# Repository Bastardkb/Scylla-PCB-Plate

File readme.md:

# Scylla PCB - plate

Flexible PCB made for the Scylla.

With per-key RGB.

This repository contains all files necessary to order a PCB.

If you want to modify the design files, the Kicad sources are included.
<!-- If you just want to order the PCBs, check out the Release section which contain the gerber files. -->

## How to order

Order with a 0.6mm or 0.8mm PCB thickness

## License

Licensed under CC BY-NC-SA 4.0
Copyright Quentin Lebastard 2021

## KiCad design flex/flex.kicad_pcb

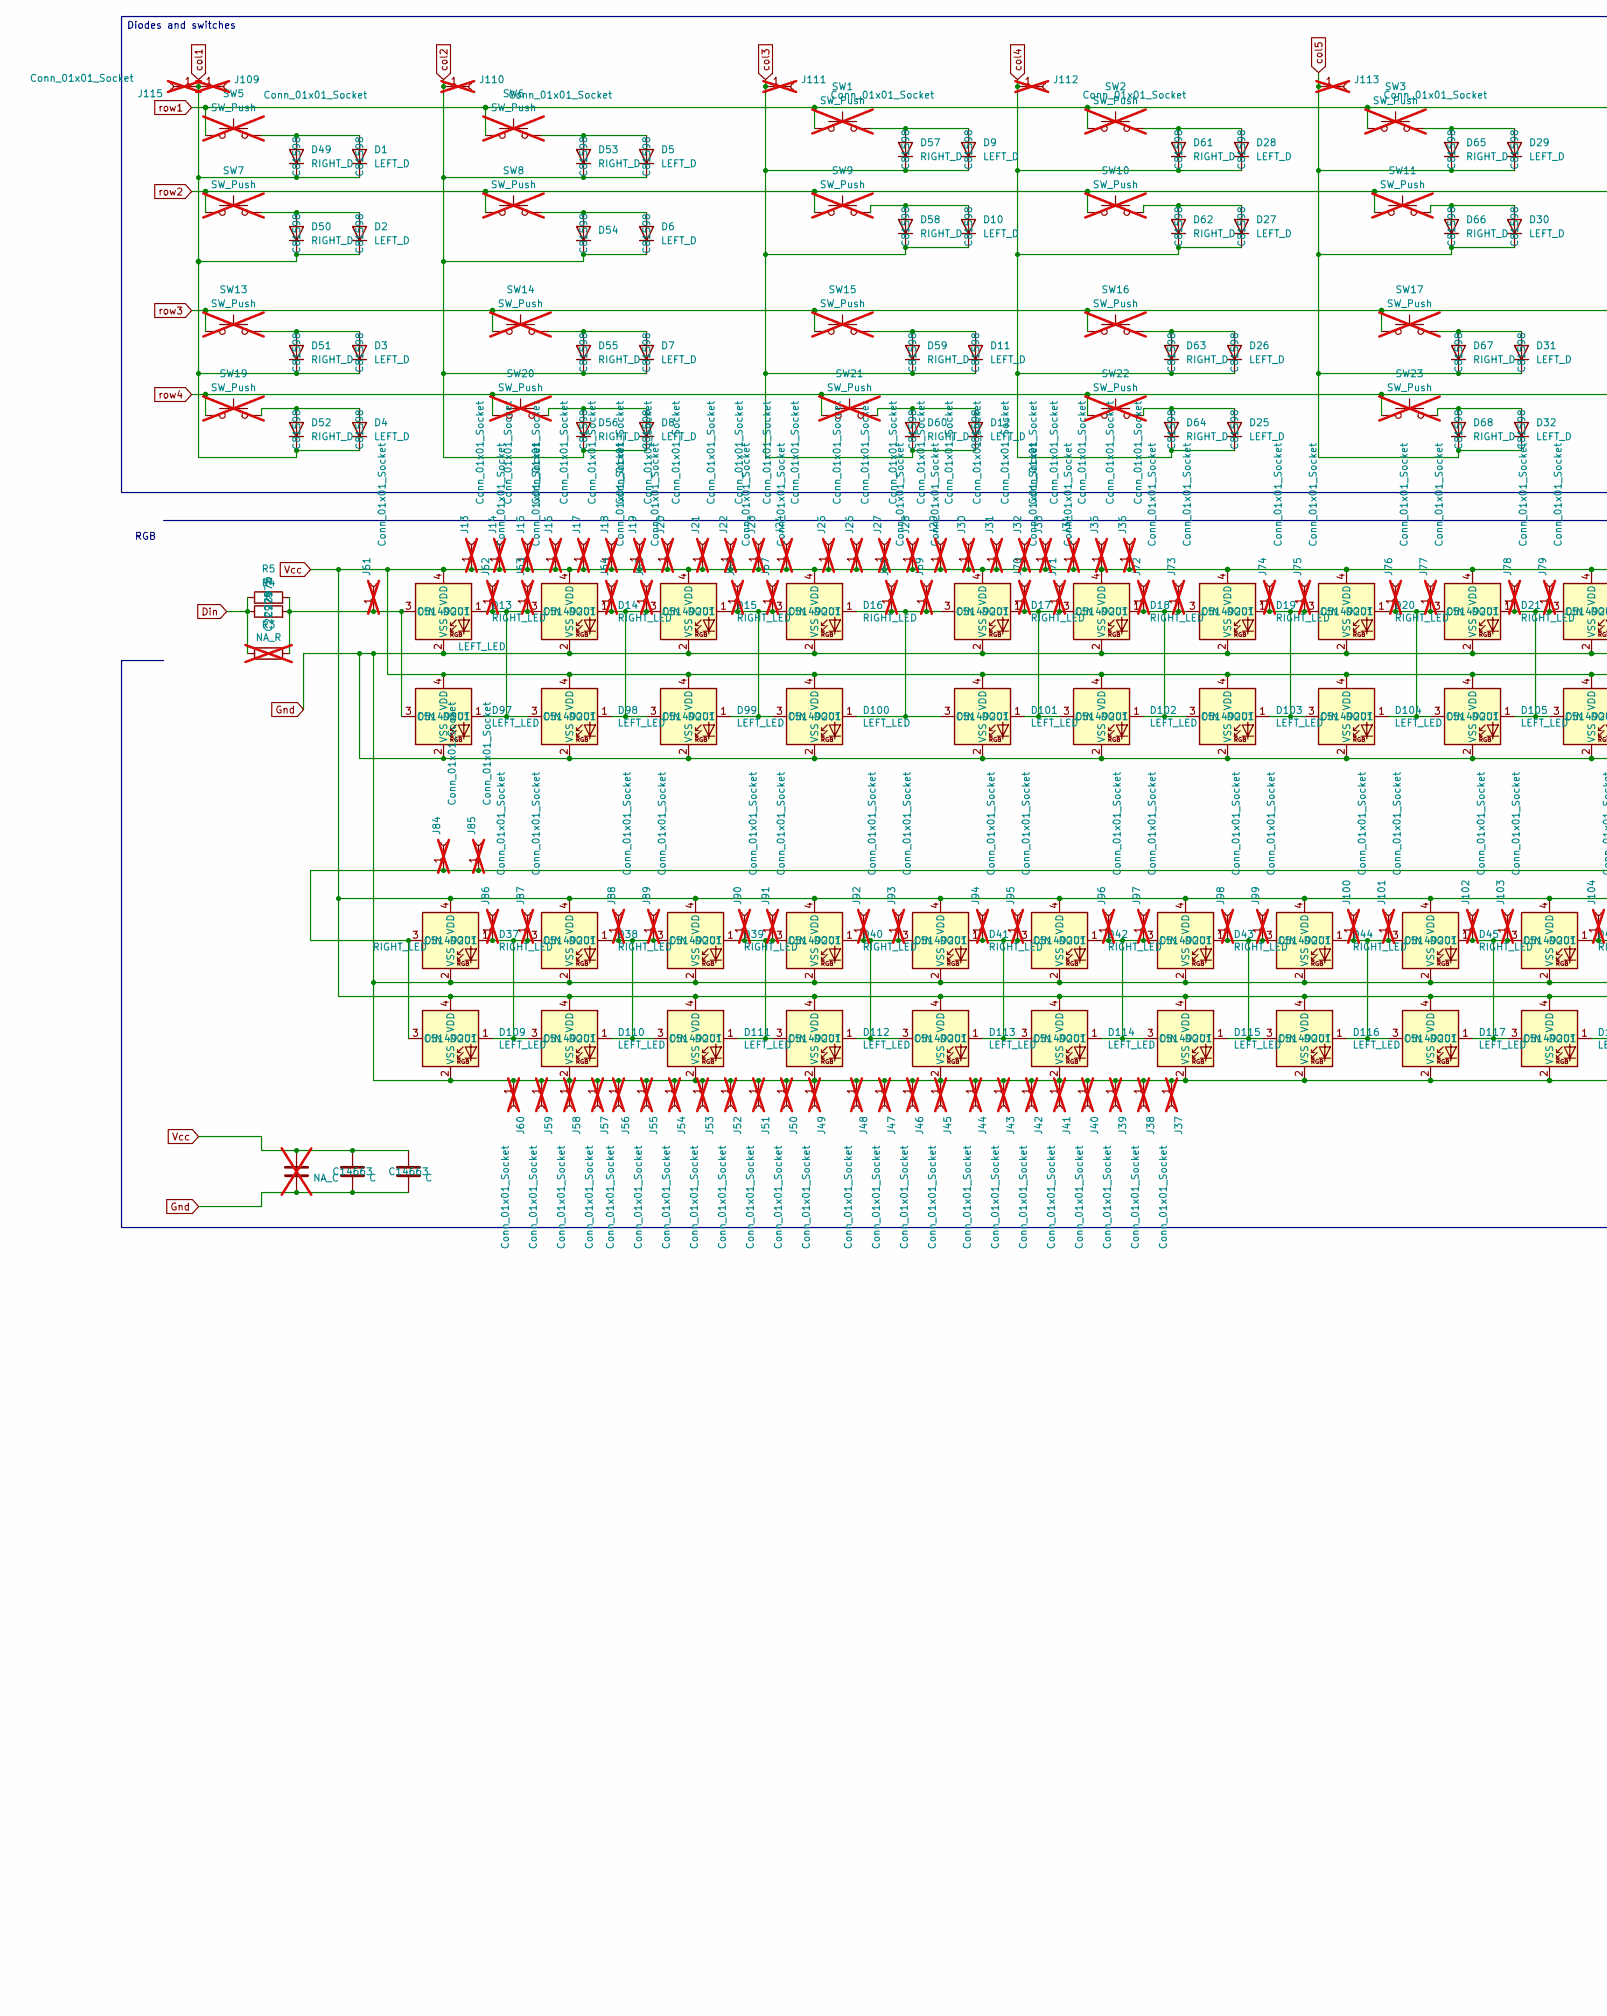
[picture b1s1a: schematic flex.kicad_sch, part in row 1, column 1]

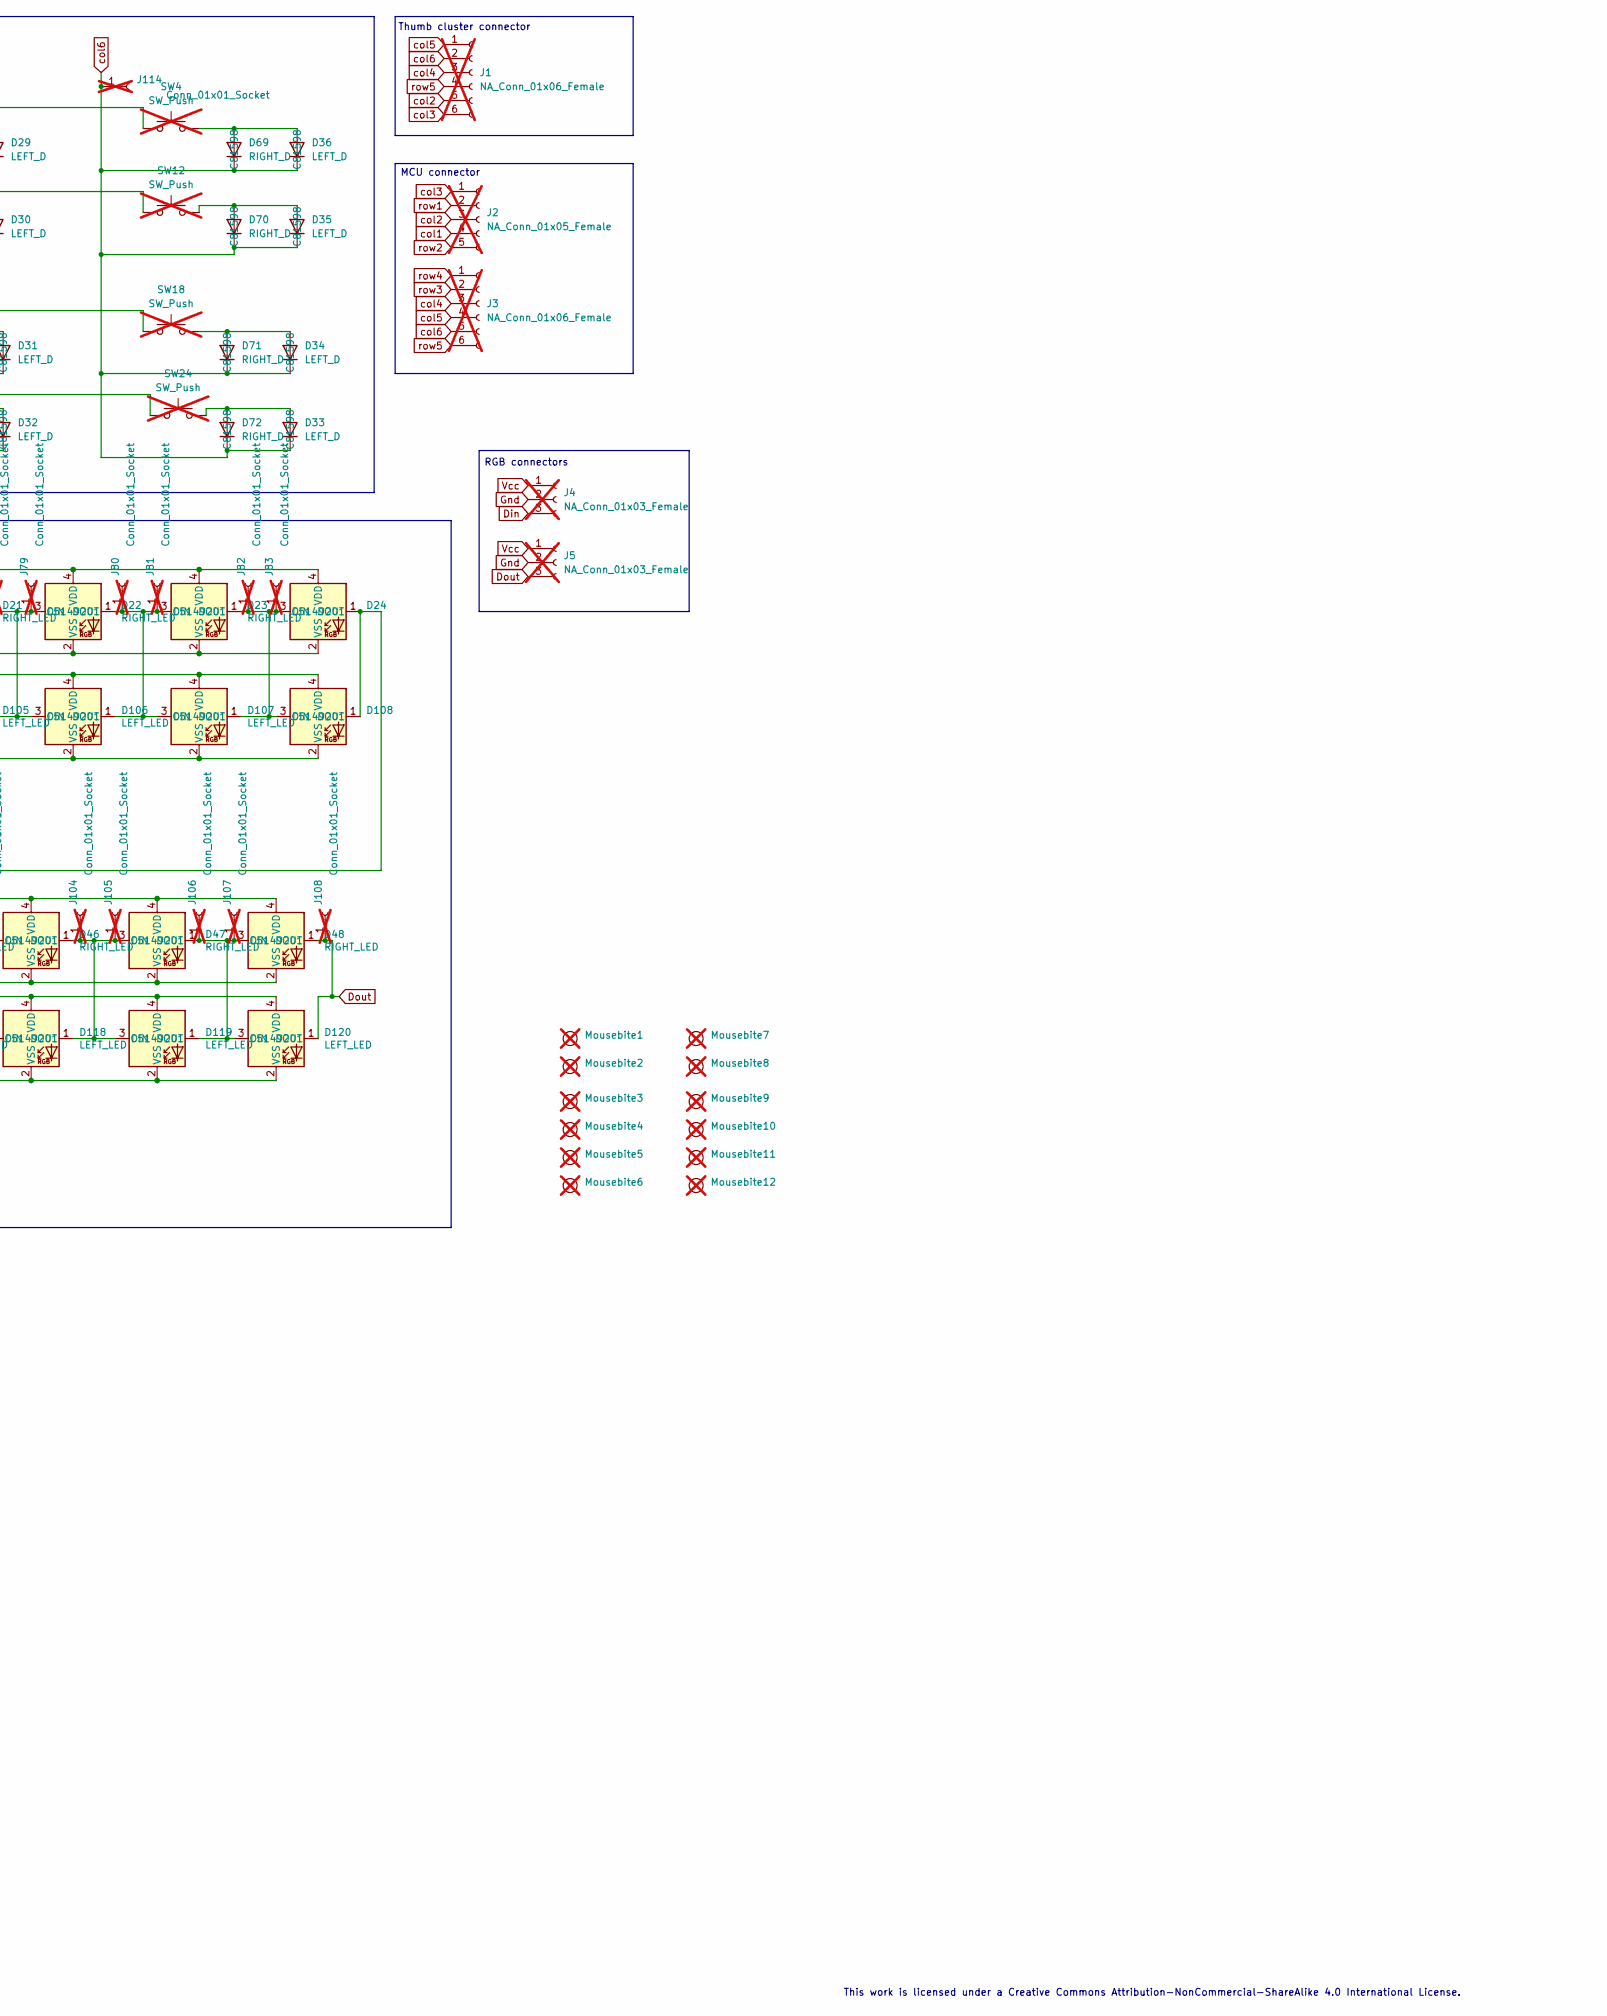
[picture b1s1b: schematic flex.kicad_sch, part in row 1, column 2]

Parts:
C3: NA_C; C_SOD123; not fitted
C4, C5: C; C_0603_1608Metric; LCSC C14663
D1, D2, D3, D4, D5, D6, D7, D8, D9, D10, D11, D12, D25, D26, D27, D28, D29, D30, D31, D32, D33, D34, D35, D36: LEFT_D; SOD123_assembly; LCSC C81598
D13, D14, D15, D16, D17, D18, D19, D20, D21, D22, D23, D24, D37, D38, D39, D40, D41, D42, D43, D44, D45, D46, D47, D48: RIGHT_LED; SK6812_mini_e_corners; LCSC C5149201
D49, D50, D51, D52, D53, D54, D55, D56, D57, D58, D59, D60, D61, D62, D63, D64, D65, D66, D67, D68, D69, D70, D71, D72: RIGHT_D; SOD123_assembly; LCSC C81598
D97, D98, D99, D100, D101, D102, D103, D104, D105, D106, D107, D108, D109, D110, D111, D112, D113, D114, D115, D116, D117, D118, D119, D120: LEFT_LED; SK6812_mini_e_corners_noedgecuts; LCSC C5149201
J1, J3: NA_Conn_01x06_Female; PinHeader_1x06_P2.54mm_Vertical; not fitted
J2: NA_Conn_01x05_Female; PinHeader_1x05_P2.54mm_Vertical; not fitted
J4, J5: NA_Conn_01x03_Female; PinHeader_1x03_P2.54mm_Vertical; not fitted
J13, J14, J15, J16, J17, J18, J19, J20, J21, J22, J23, J24, J25, J26, J27, J28, J29, J30, J31, J32, J33, J34, J35, J36: Conn_01x01_Socket; PinHeader_1x01_P1.27mm_Vertical_VCC; not fitted
J37, J38, J39, J40, J41, J42, J43, J44, J45, J46, J47, J48, J49, J50, J51, J52, J53, J54, J55, J56, J57, J58, J59, J60: Conn_01x01_Socket; PinHeader_1x01_P1.27mm_Vertical_GND; not fitted
J61, J63, J65, J67, J69, J71, J73, J75, J77, J79, J81, J83, J84, J87, J89, J91, J93, J95, J97, J99, J101, J103, J105, J107: Conn_01x01_Socket; PinHeader_1x01_P1.27mm_Vertical_IN; not fitted
J62, J64, J66, J68, J70, J72, J74, J76, J78, J80, J82, J85, J86, J88, J90, J92, J94, J96, J98, J100, J102, J104, J106, J108: Conn_01x01_Socket; PinHeader_1x01_P1.27mm_Vertical_OUT; not fitted
J109, J110, J111, J112, J113, J114, J115: Conn_01x01_Socket; PinHeader_1x01_P1.27mm_Vertical; not fitted
Mousebite1, Mousebite2, Mousebite3, Mousebite4, Mousebite5, Mousebite6, Mousebite7, Mousebite8, Mousebite9, Mousebite10, Mousebite11, Mousebite12: mousebite; not fitted
R3: NA_R; R_SOD123; not fitted
R4, R5: R; R_0603_1608Metric; LCSC C22975
SW1, SW2, SW3, SW4, SW5, SW6, SW7, SW8, SW9, SW10, SW11, SW12, SW13, SW14, SW15, SW16, SW17, SW18, SW19, SW20, SW21, SW22, SW23, SW24: SW_Push; SW_MX_reversible; not fitted

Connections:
Din: J4.3, R3.1, R4.1, R5.1
Dout: D48.1 (DOUT), D120.1 (DOUT), J5.3, J108.1
Gnd: C3.2, C4.2, C5.2, D13.2 (VSS), D14.2 (VSS), D15.2 (VSS), D16.2 (VSS), D17.2 (VSS), D18.2 (VSS), D19.2 (VSS), D20.2 (VSS), D21.2 (VSS), D22.2 (VSS), D23.2 (VSS), D24.2 (VSS), D37.2 (VSS), D38.2 (VSS), D39.2 (VSS), D40.2 (VSS), D41.2 (VSS), D42.2 (VSS), D43.2 (VSS), D44.2 (VSS), D45.2 (VSS), D46.2 (VSS), D47.2 (VSS), D48.2 (VSS), D97.2 (VSS), D98.2 (VSS), D99.2 (VSS), D100.2 (VSS), D101.2 (VSS), D102.2 (VSS), D103.2 (VSS), D104.2 (VSS), D105.2 (VSS), D106.2 (VSS), D107.2 (VSS), D108.2 (VSS), D109.2 (VSS), D110.2 (VSS), D111.2 (VSS), D112.2 (VSS), D113.2 (VSS), D114.2 (VSS), D115.2 (VSS), D116.2 (VSS), D117.2 (VSS), D118.2 (VSS), D119.2 (VSS), D120.2 (VSS), J4.2, J5.2, J37.1, J38.1, J39.1, J40.1, J41.1, J42.1, J43.1, J44.1, J45.1, J46.1, J47.1, J48.1, J49.1, J50.1, J51.1, J52.1, J53.1, J54.1, J55.1, J56.1, J57.1, J58.1, J59.1, J60.1
unnamed: D1.2 (A), D49.2 (A), SW5.2
unnamed: D2.2 (A), D50.2 (A), SW7.2
unnamed: D3.2 (A), D51.2 (A), SW13.2
unnamed: D4.2 (A), D52.2 (A), SW19.2
unnamed: D5.2 (A), D53.2 (A), SW6.2
unnamed: D10.2 (A), D58.2 (A), SW9.2
unnamed: D11.2 (A), D59.2 (A), SW15.2
unnamed: D12.2 (A), D60.2 (A), SW21.2
unnamed: D13.3 (DIN), D97.3 (DIN), J61.1, R3.2, R4.2, R5.2
unnamed: D13.1 (DOUT), D14.3 (DIN), D97.1 (DOUT), D98.3 (DIN), J62.1, J63.1
unnamed: D14.1 (DOUT), D15.3 (DIN), D98.1 (DOUT), D99.3 (DIN), J64.1, J65.1
unnamed: D25.2 (A), D64.2 (A), SW22.2
unnamed: D26.2 (A), D63.2 (A), SW16.2
unnamed: D27.2 (A), D62.2 (A), SW10.2
unnamed: D28.2 (A), D61.2 (A), SW2.2
unnamed: D29.2 (A), D65.2 (A), SW3.2
unnamed: D30.2 (A), D66.2 (A), SW11.2
unnamed: D31.2 (A), D67.2 (A), SW17.2
unnamed: D32.2 (A), D68.2 (A), SW23.2
unnamed: D33.2 (A), D72.2 (A), SW24.2
unnamed: D34.2 (A), D71.2 (A), SW18.2
unnamed: D35.2 (A), D70.2 (A), SW12.2
unnamed: D36.2 (A), D69.2 (A), SW4.2
unnamed: D6.2 (A), D54.2 (A), SW8.2
unnamed: D7.2 (A), D55.2 (A), SW14.2
unnamed: D8.2 (A), D56.2 (A), SW20.2
unnamed: D9.2 (A), D57.2 (A), SW1.2
unnamed: D15.1 (DOUT), D16.3 (DIN), D99.1 (DOUT), D100.3 (DIN), J66.1, J67.1
unnamed: D16.1 (DOUT), D17.3 (DIN), D100.1 (DOUT), D101.3 (DIN), J68.1, J69.1
unnamed: D17.1 (DOUT), D18.3 (DIN), D101.1 (DOUT), D102.3 (DIN), J70.1, J71.1
unnamed: D18.1 (DOUT), D19.3 (DIN), D102.1 (DOUT), D103.3 (DIN), J72.1, J73.1
unnamed: D19.1 (DOUT), D20.3 (DIN), D103.1 (DOUT), D104.3 (DIN), J74.1, J75.1
unnamed: D20.1 (DOUT), D21.3 (DIN), D104.1 (DOUT), D105.3 (DIN), J76.1, J77.1
unnamed: D21.1 (DOUT), D22.3 (DIN), D105.1 (DOUT), D106.3 (DIN), J78.1, J79.1
unnamed: D22.1 (DOUT), D23.3 (DIN), D106.1 (DOUT), D107.3 (DIN), J80.1, J81.1
unnamed: D23.1 (DOUT), D24.3 (DIN), D107.1 (DOUT), D108.3 (DIN), J82.1, J83.1
unnamed: D24.1 (DOUT), D37.3 (DIN), D108.1 (DOUT), D109.3 (DIN), J84.1, J85.1
unnamed: D37.1 (DOUT), D38.3 (DIN), D109.1 (DOUT), D110.3 (DIN), J86.1, J87.1
unnamed: D38.1 (DOUT), D39.3 (DIN), D110.1 (DOUT), D111.3 (DIN), J88.1, J89.1
unnamed: D39.1 (DOUT), D40.3 (DIN), D111.1 (DOUT), D112.3 (DIN), J90.1, J91.1
unnamed: D40.1 (DOUT), D41.3 (DIN), D112.1 (DOUT), D113.3 (DIN), J92.1, J93.1
unnamed: D41.1 (DOUT), D42.3 (DIN), D113.1 (DOUT), D114.3 (DIN), J94.1, J95.1
unnamed: D42.1 (DOUT), D43.3 (DIN), D114.1 (DOUT), D115.3 (DIN), J96.1, J97.1
unnamed: D43.1 (DOUT), D44.3 (DIN), D115.1 (DOUT), D116.3 (DIN), J98.1, J99.1
unnamed: D44.1 (DOUT), D45.3 (DIN), D116.1 (DOUT), D117.3 (DIN), J100.1, J101.1
unnamed: D45.1 (DOUT), D46.3 (DIN), D117.1 (DOUT), D118.3 (DIN), J102.1, J103.1
unnamed: D46.1 (DOUT), D47.3 (DIN), D118.1 (DOUT), D119.3 (DIN), J104.1, J105.1
unnamed: D47.1 (DOUT), D48.3 (DIN), D119.1 (DOUT), D120.3 (DIN), J106.1, J107.1
Vcc: C3.1, C4.1, C5.1, D13.4 (VDD), D14.4 (VDD), D15.4 (VDD), D16.4 (VDD), D17.4 (VDD), D18.4 (VDD), D19.4 (VDD), D20.4 (VDD), D21.4 (VDD), D22.4 (VDD), D23.4 (VDD), D24.4 (VDD), D37.4 (VDD), D38.4 (VDD), D39.4 (VDD), D40.4 (VDD), D41.4 (VDD), D42.4 (VDD), D43.4 (VDD), D44.4 (VDD), D45.4 (VDD), D46.4 (VDD), D47.4 (VDD), D48.4 (VDD), D97.4 (VDD), D98.4 (VDD), D99.4 (VDD), D100.4 (VDD), D101.4 (VDD), D102.4 (VDD), D103.4 (VDD), D104.4 (VDD), D105.4 (VDD), D106.4 (VDD), D107.4 (VDD), D108.4 (VDD), D109.4 (VDD), D110.4 (VDD), D111.4 (VDD), D112.4 (VDD), D113.4 (VDD), D114.4 (VDD), D115.4 (VDD), D116.4 (VDD), D117.4 (VDD), D118.4 (VDD), D119.4 (VDD), D120.4 (VDD), J4.1, J5.1, J13.1, J14.1, J15.1, J16.1, J17.1, J18.1, J19.1, J20.1, J21.1, J22.1, J23.1, J24.1, J25.1, J26.1, J27.1, J28.1, J29.1, J30.1, J31.1, J32.1, J33.1, J34.1, J35.1, J36.1
col1: D1.1 (K), D2.1 (K), D3.1 (K), D4.1 (K), D49.1 (K), D50.1 (K), D51.1 (K), D52.1 (K), J2.4, J109.1, J115.1
col2: D5.1 (K), D6.1 (K), D7.1 (K), D8.1 (K), D53.1 (K), D54.1 (K), D55.1 (K), D56.1 (K), J1.5, J2.3, J110.1
col3: D9.1 (K), D10.1 (K), D11.1 (K), D12.1 (K), D57.1 (K), D58.1 (K), D59.1 (K), D60.1 (K), J1.6, J2.1, J111.1
col4: D25.1 (K), D26.1 (K), D27.1 (K), D28.1 (K), D61.1 (K), D62.1 (K), D63.1 (K), D64.1 (K), J1.3, J3.3, J112.1
col5: D29.1 (K), D30.1 (K), D31.1 (K), D32.1 (K), D65.1 (K), D66.1 (K), D67.1 (K), D68.1 (K), J1.1, J3.4, J113.1
col6: D33.1 (K), D34.1 (K), D35.1 (K), D36.1 (K), D69.1 (K), D70.1 (K), D71.1 (K), D72.1 (K), J1.2, J3.5, J114.1
row1: J2.2, SW1.1, SW2.1, SW3.1, SW4.1, SW5.1, SW6.1
row2: J2.5, SW7.1, SW8.1, SW9.1, SW10.1, SW11.1, SW12.1
row3: J3.2, SW13.1, SW14.1, SW15.1, SW16.1, SW17.1, SW18.1
row4: J3.1, SW19.1, SW20.1, SW21.1, SW22.1, SW23.1, SW24.1
row5: J1.4, J3.6

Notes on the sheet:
Diodes and switches
RGB
MCU connector
Thumb cluster connector
This work is licensed under a Creative Commons Attribution-NonCommercial-ShareAlike 4.0 International License.
RGB connectors

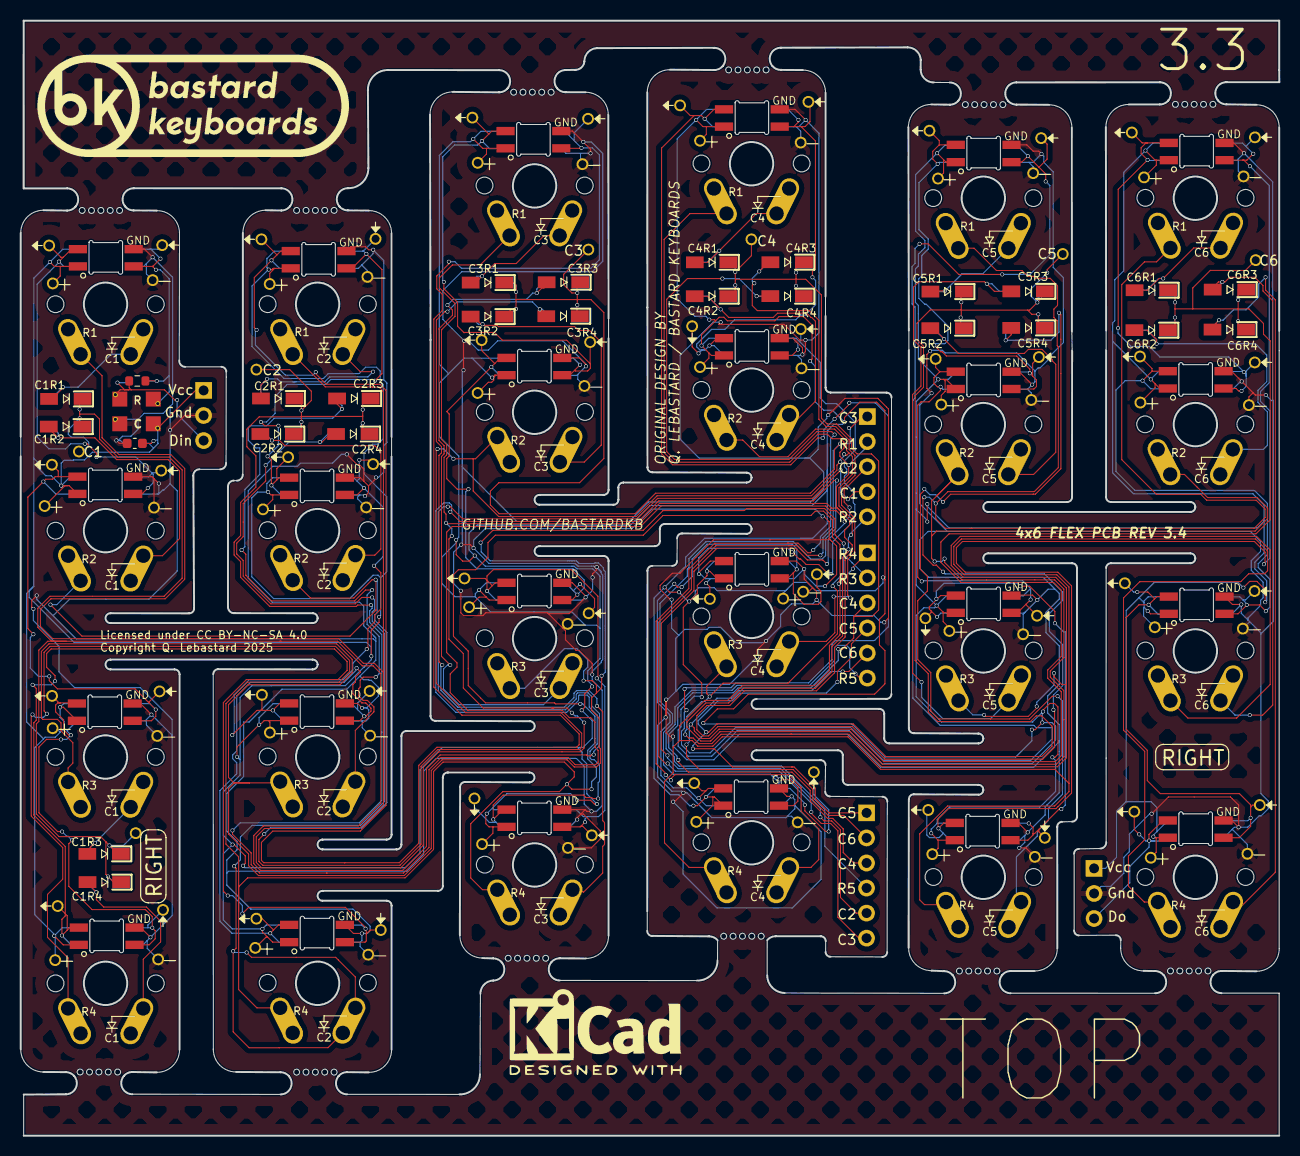
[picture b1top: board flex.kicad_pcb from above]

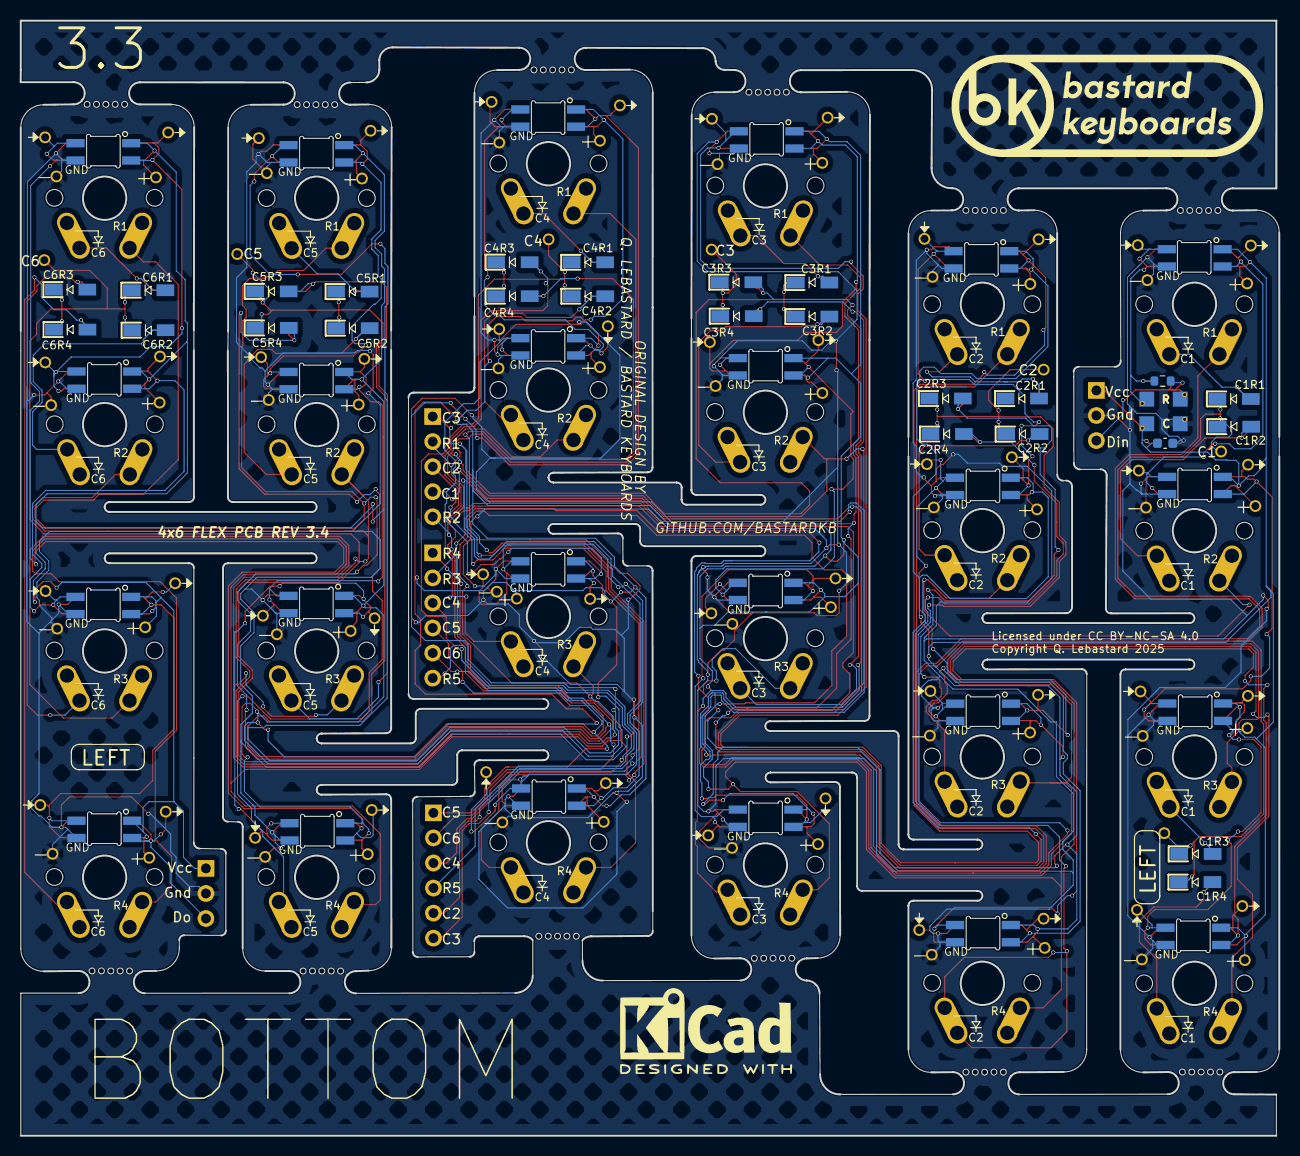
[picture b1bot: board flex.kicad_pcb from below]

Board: 2 copper layers, 127.6 x 113.0 mm, 246 parts (75 on the bottom side), 63 nets.

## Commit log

2022-02-20 add stuff
2022-02-20 edge cuts, via size
2022-02-20 cleanup
2022-02-22 revert routing
2022-02-25 silkscreen
2022-02-25 add pic
2022-02-25 update pic
2022-04-12 cleanup and reinforce c4/c5 connection
2023-03-09 rounder footprints
2023-03-09 edge cuts
2023-03-09 update diodes and leds
2023-03-09 emergency diodes
2023-03-09 routing
2023-03-15 remove zones
2023-03-15 Revert "remove zones"
    This reverts commit 77ee5344f6f81e13d1a8d3e3c47d1c087e48574b.
2023-03-15 LED thermal reliefs
2023-03-17 footprints
2023-03-17 zones
2023-04-09 DRC|
2023-05-15 version number
2023-06-17 separate into right/left diodes
2023-06-17 left/right capacitor resistor
2023-06-17 LEDs
2024-11-12 north facing LEDs
2024-11-12 remove small diodes
2024-11-12 solidify main ribbon cable connector
2024-12-06 diodes horizontal, more space for RGB
2024-12-06 switch numbering
2024-12-06 horizontal diodes
2024-12-06 more space
2024-12-08 smaller switch holes and pads
2024-12-10 bigger inner col
2024-12-10 led routing
2024-12-13 rgb footprint
2024-12-16 row/column indication on switch
2025-01-30 smaller LED corners
2025-02-04 drilled mouse bites
2025-03-11 bigger diode pads
2025-03-11 add GND/pin 1 dot to sk6812 footprint for JLC assembly
2025-03-11 move diodes further apart
2025-05-22 BOM work
2025-05-23 bigger diode lines
2025-06-18 place vcc pads
2025-06-18 place pads
2025-06-18 more placement
2025-06-18 pad placement
2025-06-18 labels
2025-06-19 connect pads
2025-06-19 DRC, silkscreen
2025-06-19 reinforce tracks
2025-06-19 silkscreen fixes
2025-09-29 smaller traces and vias
2025-09-29 switch back to bigger vias
2025-09-29 remove row connections on middle column
2025-09-30 remake c3 row routing

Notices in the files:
flex/flex.kicad_pcb:
Copyright Q. Lebastard 2025
flex/flex.kicad_sch:
Copyright Quentin Lebastard 2022
